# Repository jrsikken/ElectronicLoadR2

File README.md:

# Hardware of Jasper's Electronic Load R2
This is a Arduino compatible Electronic Load. It is intended for testing DC power supplies, solar panels and batteries. 
I am selling on Tindie https://www.tindie.com/products/jaspersikken/jaspers-electronic-load-r2/
Technical details are also found there.

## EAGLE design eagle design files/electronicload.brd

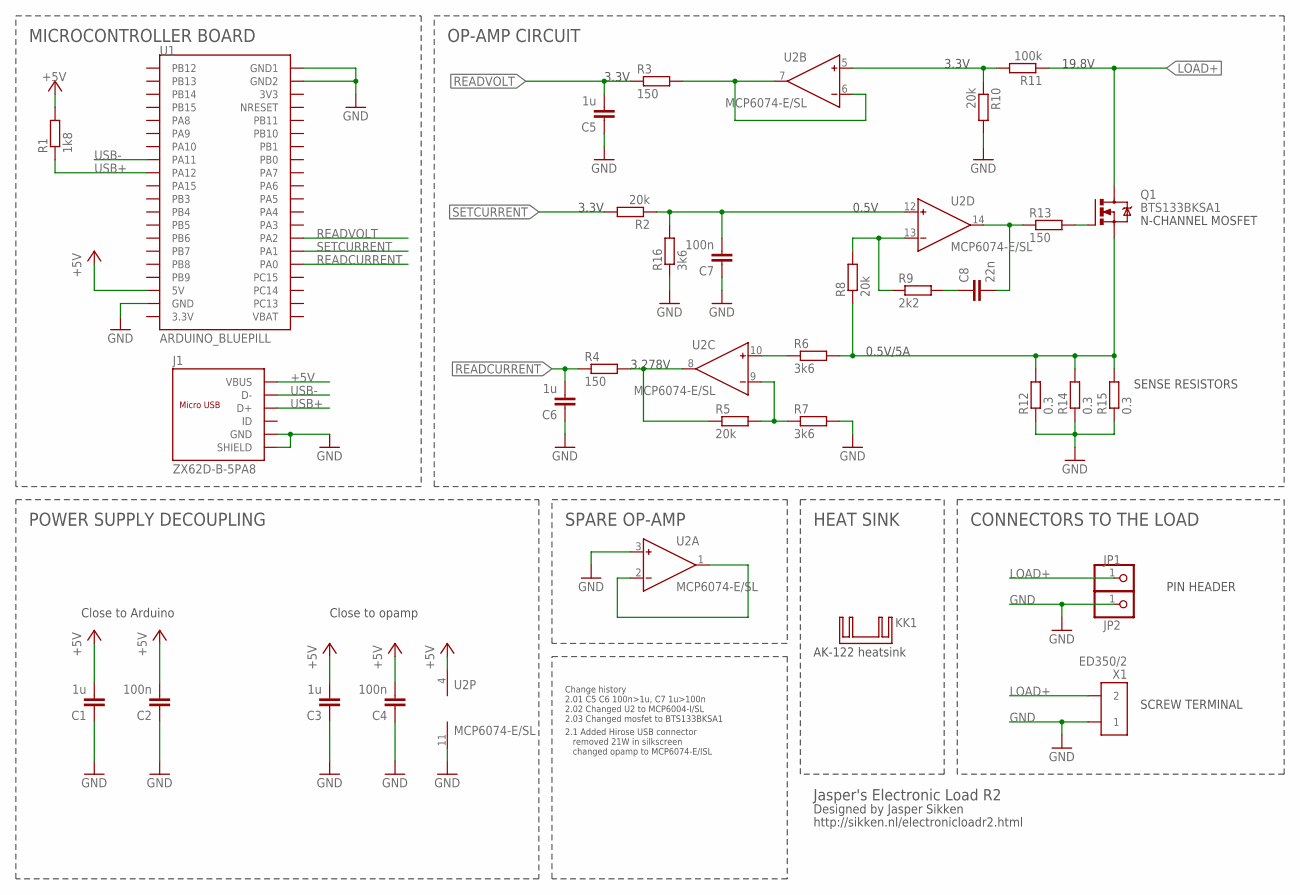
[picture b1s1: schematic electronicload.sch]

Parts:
C1, C3: 1u; C0603K; TOLERANCE 10%; VOLTAGE 16V; DIGIKEY 311-1444-1-ND
C2, C4: 100n; C0603K; TOLERANCE 10%; VOLTAGE 50V; DIGIKEY 445-7456-1-ND
C5, C6: 1u; C0603K; TOLERANCE 10%; VOLTAGE 50V; DIGIKEY 445-7456-1-ND
C7: 100n; C0603K; TOLERANCE 10%; VOLTAGE 50V; DIGIKEY 445-12511-1-ND
C8: 22n; C0603K; TOLERANCE 10%; VOLTAGE 25V; DIGIKEY 445-12490-1-ND
J1: ZX62D-B-5PA8; MICRO-USB5+6P-SMD-0.65-AB
JP1, JP2: PINHD-1X1; 1X01
KK1: SK129; SK129-HOLE
Q1: BTS133BKSA1; TO220BV; DIGIKEY BTS133BKSA1-ND
R1: 1k8; R0603; DIGIKEY RMCF0603JT18K0CT-ND
R2, R8: 20k; R0603; DIGIKEY RMCF0603JT18K0CT-ND
R3, R4, R13: 150; R0603; DIGIKEY RMCF0603JT150RCT-ND
R5: 20k; R0603; DIGIKEY RMCF0603JT180KCT-ND
R6, R7: 3k6; R0603; DIGIKEY RMCF0603JT20K0CT-ND
R9: 2k2; R0603; DIGIKEY RMCF0603JT2K20CT-ND
R10: 20k; R0603; DIGIKEY RMCF0603JT20K0CT-ND
R11: 100k; R0603; DIGIKEY RMCF0603JT100KCT-ND
R12, R14, R15: 0.3; R2512
R16: 3k6; R0603; DIGIKEY RMCF0603JT18K0CT-ND
U1: ARDUINO_BLUEPILL
U2: MCP6074-E/SL; SO14
X1: ED350/2

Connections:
+5V: C1.2, C2.2, C3.2, C4.2, J1.1 (VBUS), R1.2, U1.P$37 (5V), U2.4 (V+)
GATE: Q1.G, R13.2
GND: C1.1, C2.1, C3.1, C4.1, C5.1, C6.1, C7.1, J1.5 (GND), J1.P1 (SHIELD), J1.P2 (SHIELD), J1.P3 (SHIELD), J1.P4 (SHIELD), J1.P5 (SHIELD), J1.P6 (SHIELD), JP2.1, R7.2, R10.2, R12.1, R14.1, R15.1, R16.1, U1.P$18 (GND2), U1.P$19 (GND1), U1.P$38 (GND), U2.3 (IN+), U2.11 (V-), X1.P$1 (1)
LOAD+: JP1.1, Q1.D, R11.1, X1.P$2 (2)
unnamed: C8.2, R13.1, U2.14 (OUT)
unnamed: R3.2, U2.6 (IN-), U2.7 (OUT)
unnamed: R6.1, U2.10 (IN+)
unnamed: R8.2, R9.1, U2.13 (IN-)
unnamed: R10.1, R11.2, U2.5 (IN+)
unnamed: C7.2, R2.1, R16.2, U2.12 (IN+)
unnamed: R5.2, R7.1, U2.9 (IN-)
unnamed: R4.2, R5.1, U2.8 (OUT)
unnamed: C8.1, R9.2
unnamed: U2.1 (OUT), U2.2 (IN-)
READCURRENT: C6.2, R4.1, U1.P$4 (PA0)
READVOLT: C5.2, R3.1, U1.P$6 (PA2)
SENSE: Q1.S, R6.2, R8.1, R12.2, R14.2, R15.2
SETCURRENT: R2.2, U1.P$5 (PA1)
USB+: J1.3 (D+), R1.1, U1.P$28 (PA12)
USB-: J1.2 (D-), U1.P$27 (PA11)

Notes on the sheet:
POWER SUPPLY DECOUPLING
PIN HEADER
SCREW TERMINAL
SENSE RESISTORS
N-CHANNEL MOSFET
3.3V
19.8V
0.5V
0.5V/5A
3.278V
Designed by Jasper Sikken
http://sikken.nl/electronicloadr2.html
Close to Arduino
Close to opamp
HEAT SINK
SPARE OP-AMP
CONNECTORS TO THE LOAD
MICROCONTROLLER BOARD
OP-AMP CIRCUIT
AK-122 heatsink
Jasper's Electronic Load R2
Change history 2.01 C5 C6 100n>1u, C7 1u>100n 2.02 Changed U2 to MCP6004-I/SL 2.03 Changed mosfet to BTS133BKSA1
2.1 Added Hirose USB connector removed 21W in silkscreen changed opamp to MCP6074-E/ISL

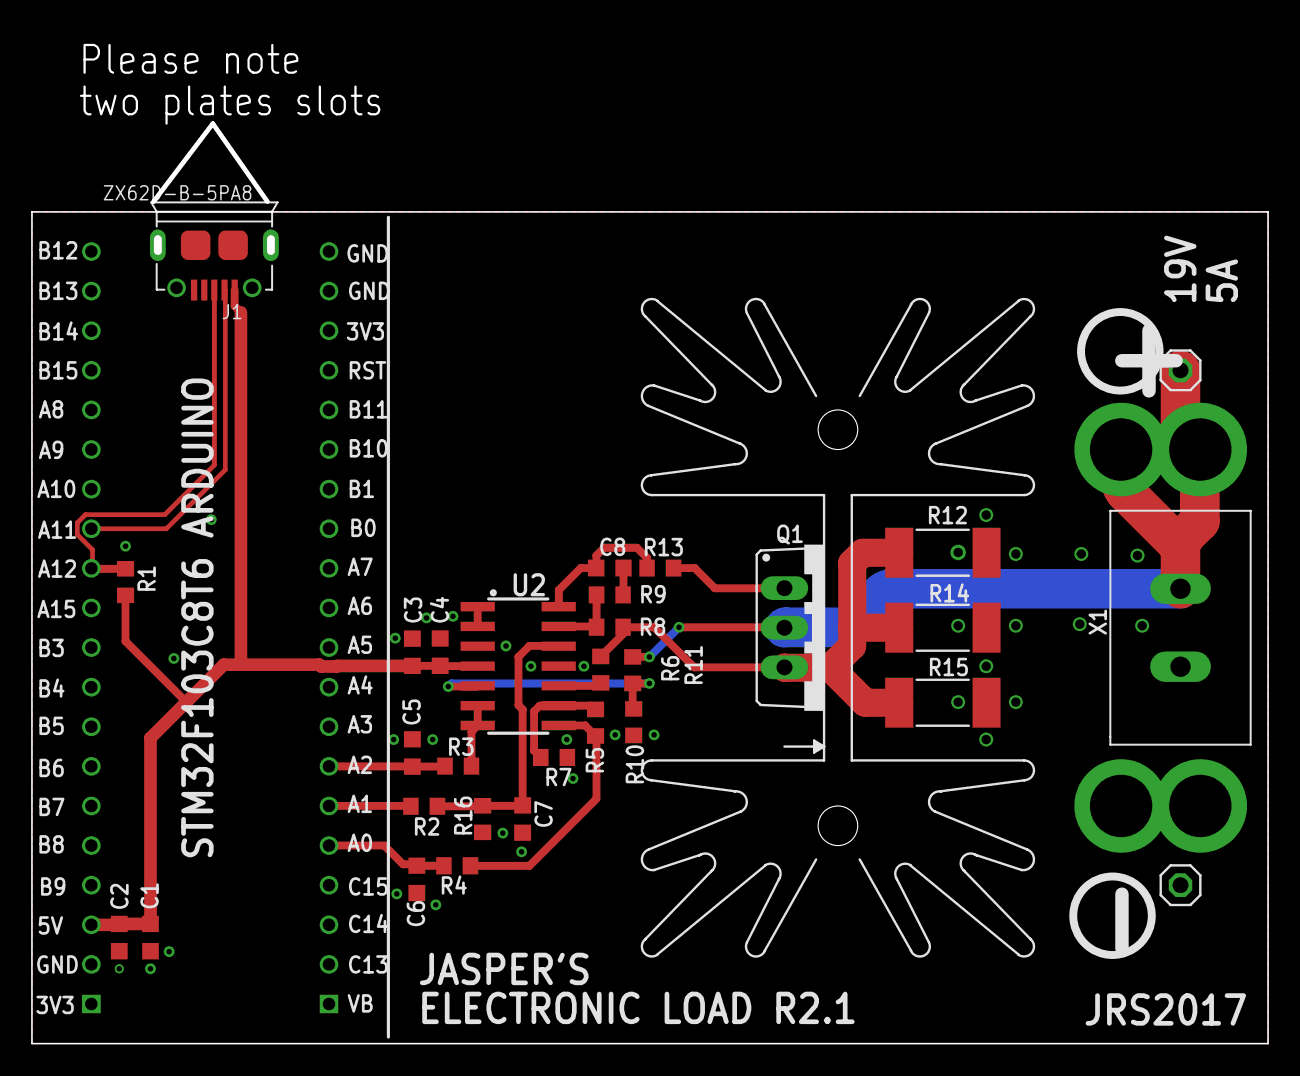
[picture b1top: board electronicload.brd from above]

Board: 2 copper layers, 79.3 x 53.3 mm, 32 parts (0 on the bottom side), 20 nets.

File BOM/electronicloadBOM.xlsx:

Qty | Value | Package | Parts | Description | TOLERANCE | MF | MPN | Ebay
3 | 0.3R | R2512 | R12, R14, R15 | Resistor | 0.01 |  |  | http://www.ebay.com/itm/100PCS-2512-6432-1W-0-3-ohm-R300-0-3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
1 | 100k | R0603 | R11 | RESISTOR, European symbol | 0.01 |  |  | http://www.ebay.com/itm/200Pcs-0603-SMD-Resistor-Resistors-1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
3 | 100n | C0603 | C2, C4, C7 | CAPACITOR, European symbol | 0.1 |  |  | http://www.ebay.com/itm/100PCS-0603-1608-100n-100nF-104K-10-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
3 | 150R | R0603 | R3, R4, R13 | RESISTOR, European symbol | 0.01 |  |  | http://www.ebay.com/itm/200PCS-150R-150-ohm-Ω-1-1-10W-SMD-Ch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
1 | 1k8 | R0603 | R1 | RESISTOR, European symbol | 0.01 |  |  | http://www.ebay.com/itm/100pcs-0603-SMD-Resistor-1-8K-ohm-1K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
4 | 1u | C0603 | C1, C3, C5, C6 | CAPACITOR, European symbol | 0.1 |  |  | http://www.ebay.com/itm/100PCS-1uF-105K-10-16V-X7R-0603-1608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
4 | 20k | R0603 | R2, R5, R8, R10 | RESISTOR, European symbol | 0.01 |  |  | http://www.ebay.com/itm/200Pcs-0603-SMD-Resistor-Resistors-1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
1 | 22n | C0603 | C8 | CAPACITOR, European symbol | 0.1 |  |  | http://www.ebay.com/itm/100PCS-22nF-223-10-50V-X7R-0603-1608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
1 | 2k2 | R0603 | R9 | RESISTOR, European symbol | 0.01 |  |  | http://www.ebay.com/itm/200Pcs-0603-SMD-Resistor-Resistors-1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
3 | 3k6 | R0603 | R6, R7, R16 | RESISTOR, European symbol | 0.01 |  |  | http://www.ebay.com/itm/200Pcs-0603-SMD-Resistor-Resistors-1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
1 | MCP6074-E/SL | SO14 | U2 | Op Amp |  | Microchip | MCP6074-E/SL
1 | ARDUINO_BLUEPILL | ARDUINO_BLUEPILL | U1 | PCB assembly |  |  |  | http://www.ebay.com/itm/10PCS-STM32F103C8T6-ARM-STM32-Minimu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
1 | KF128-2P | KF128-2P | X1 | KF128-2P (5.08 mm) TERMINAL BLOCK |  |  |  | http://www.ebay.com/itm/20pcs-2Pin-Plug-in-Terminal-Block-DG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
1 | BTS133BKSA1 | TO220BV | Q1 | Smart low side power switch |  | Infineon | BTS133BKSA1 | There's are fake ones on ebay. Please buy from Digikey, Mouser, Farnell etc.
1 | AK-122 | SK129-HOLE | KK1 | Aluminum Heatsink Ak-122 H=45mm 42x25x45mm Color=Natural TO-TO-220 |  |  |  | http://www.ebay.com/itm/20pc-Aluminum-Heatsink-Ak-122-H-45mm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
2 | 20p female header |  |  | 2.54mm Pitch 1X20 Pin Female Single Row Straight Header Connector |  |  |  | http://www.ebay.com/itm/20pcs-2-54mm-Pitch-1X-20-Pin-Female-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
4 | rubber feet | 8 x 2.5 mm |  | Adhesive Silicone Feet Bumpers |  |  |  | http://www.ebay.com/itm/100PCS-Self-Adhesive-Rubber-Feet-Cle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
1 | heat sink mounting kit |  |  | TO-220 Heatsink Mounting Insulator Kit |  |  |  | http://www.ebay.com/itm/20-sets-TO-220-Heatsink-Mounting-Ins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
1 | CE sticker |  |  | CE Adhesive Sticker |  |  |  | http://www.ebay.com/itm/3-Sheets-CE-Certificated-Label-Stick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
1 | PCB R2 |  |  | PCB Jasper's Electronic Load R2

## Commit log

2017-10-17 Added eagle design files, and schematic in pdf
2017-10-17 added gerber and BOM
2017-10-22 R2.01 Changed capacitor values.
2017-10-22 R2.01 changed C5, C6, C7
2017-11-01 R2.02 changed opamp to MCP6004-I/SL
2017-11-01 Add location where I sell the device
2017-11-10 2.03 Changed mosfet to the much more robust BTS133
2017-12-15 changed opamp from MCP6004 to MCP6074 (much lower input voltage offset)
2017-12-17 R2.1 New PCB design, added USB connector, changed mosfet from MCP6004 to MCP6074-E/SL
2018-01-05 added schematic R2.1 in pdf format
2018-03-21 BOM R2.1.1 Added extra large heat sink (31W) to the BOM
